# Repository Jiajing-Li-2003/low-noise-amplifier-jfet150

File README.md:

# low-noise-amplifier-jfet150
Open source low-noise amplifier project using JFET150

# 🔊 Low-Noise Amplifier (LNA) Project – JFET150 + OPA211 + Differential Stage

This project documents the design and testing of a **low-noise amplifier (LNA)**, based on a JFET input stage followed by a precision op-amp (OPA211), and a second-stage differential amplifier.

Everything is **open source** and shared for learning, experimentation, and collaboration.

---

## 📌 Table of Contents

- [Overview](#overview)
- [Features](#features)
- [Circuit Design](#circuit-design)
- [Measurements](#measurements)
- [Bill of Materials](#bill-of-materials)
- [Schematic and PCB](#schematic-and-pcb)
- [Usage](#usage)
- [License](#license)
- [Author](#author)

---

## 🔍 Overview

This two-stage amplifier is designed for applications requiring ultra-low noise and high gain:

1. **Low-noise preamp** based on a JFET transistor (JFET150) + OPA211 with ~40 dB gain
2. **Differential amplifier** that adds another 20 dB gain and rejects common-mode noise

---

## ⚙️ Features

| Parameter              | Value                  |
|------------------------|------------------------|
| Total Gain             | ~60 dB (×1000)         |
| Input Noise            | [2 nV/√Hz, @1kHz]      |
| Bandwidth              | [10 Hz – 100 kHz]      |
| Supply Voltage         | 0V-5V                  |
| Input Impedance        | >? MΩ                  |
| Output Impedance       | ~??? Ω                 |

---

## 🔧 Circuit Design

### 🔹 Stage 1 – Low-Noise Preamp

- JFET input (JFET150)
- Precision Op-Amp (OPA211)
- Gain: ~40 dB
- Focus: low noise, high input impedance

### 🔸 Stage 2 – Differential Amplifier

- Differential op-amp topology
- Gain: ~20 dB
- Focus: common-mode noise rejection

---

## 📊 Measurements

The transfer function measurements were performed using two 20 dB attenuators, resulting in a total attenuation of 33 dB applied to the gain:

This is the transfer function of the first stage (blue curve):

This is the transfer function of the second stage:

And there we have the input noise of the amplifier

---

## 🖨️ Schematic and PCB

Browse PCB and schematics online [here](https://kicanvas.org/?github=https%3A%2F%2Fgithub.com%2FJiajing-Li-2003%2Flow-noise-amplifier-jfet150%2Fblob%2Fmain%2Fhardware%2Fampli%2520jfe150%2520searchcoil.kicad_pro).

Files are in the `hardware/` directory.

---

## 🔌 Usage

1. **Power Supply**: +5 V regulated
2. **Input**: Search Coil (a magnetometer)
3. **Output**: Connect to oscilloscope or ADC

> ⚠️ Make sure to use a proper power supply with current limiting

---

## 🪪 License

This project is licensed under the **MIT License** – see the [LICENSE](./LICENSE) file for details.

---

## 🙋 Contributions

Feel free to fork, open issues, or submit pull requests if you want to improve or adapt this project.

---

## 👨‍🔬 Author

Designed by Li Jiajing, This project was carried out during an assistant engineer internship under the supervision of Alexis Jeandet at the Plasma Physics Laboratory (LPP).

---

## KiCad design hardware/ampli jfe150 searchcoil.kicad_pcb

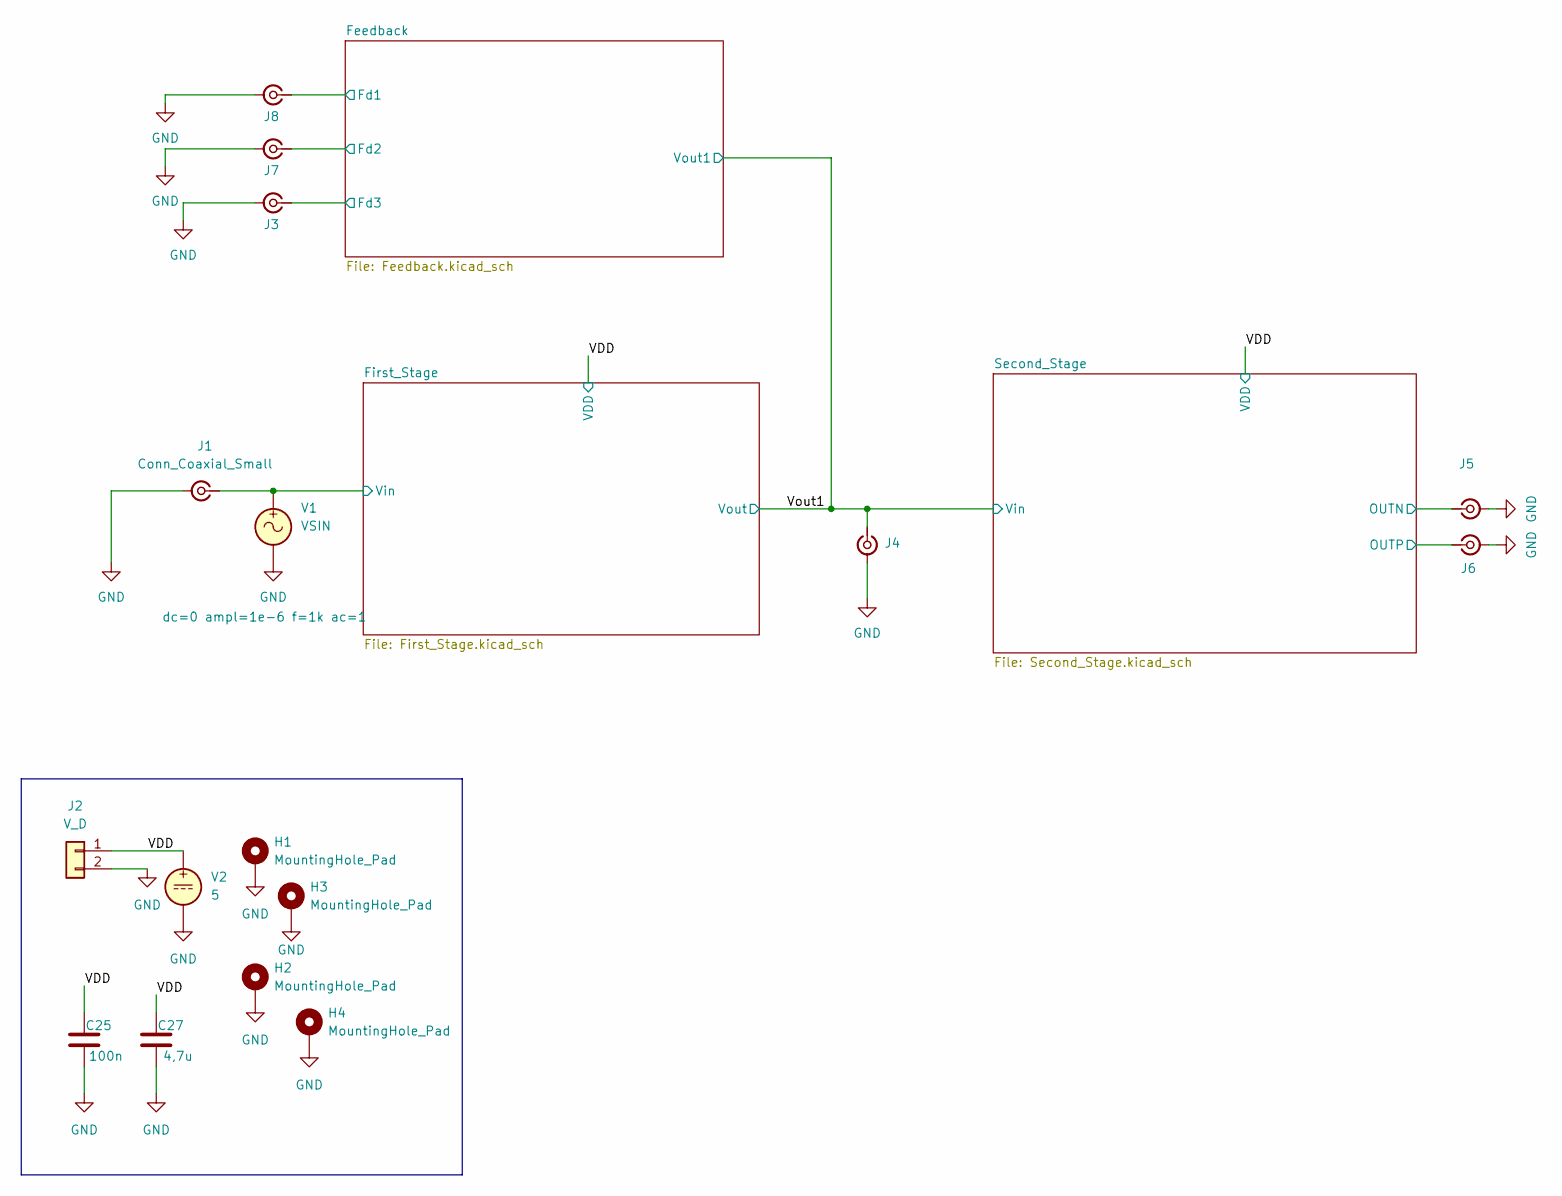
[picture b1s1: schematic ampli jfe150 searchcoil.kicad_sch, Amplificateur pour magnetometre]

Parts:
C25: 100n; C_0603_1608Metric_Pad1.08x0.95mm_HandSolder
C27: 4,7u; C_1206_3216Metric_Pad1.33x1.80mm_HandSolder
H1, H2, H3, H4: MountingHole_Pad; MountingHole_2.2mm_M2_DIN965_Pad
J1, J3, J4, J5, J6, J7, J8: Conn_Coaxial_Small; SMB_Jack_Vertical
J2: V_D; PinHeader_1x02_P2.54mm_Vertical
V1: VSIN
V2: 5

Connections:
/Feedback/Fd1: J8.1 (In); also elsewhere on the board
/Feedback/Fd2: J7.1 (In); also elsewhere on the board
/Feedback/Fd3: J3.1 (In); also elsewhere on the board
/First_Stage/Vin: J1.1 (In), V1.1; also elsewhere on the board
/Second_Stage/OUTN: J5.1 (In); also elsewhere on the board
/Second_Stage/OUTP: J6.1 (In); also elsewhere on the board
/VDD: C25.1, C27.1, J2.1, V2.1; also elsewhere on the board
/Vout1: J4.1 (In); also elsewhere on the board
GND: C25.2, C27.2, H1.1, H2.1, H3.1, H4.1, J1.2 (Ext), J2.2, J3.2 (Ext), J4.2 (Ext), J5.2 (Ext), J6.2 (Ext), J7.2 (Ext), J8.2 (Ext), V1.2, V2.2; also elsewhere on the board

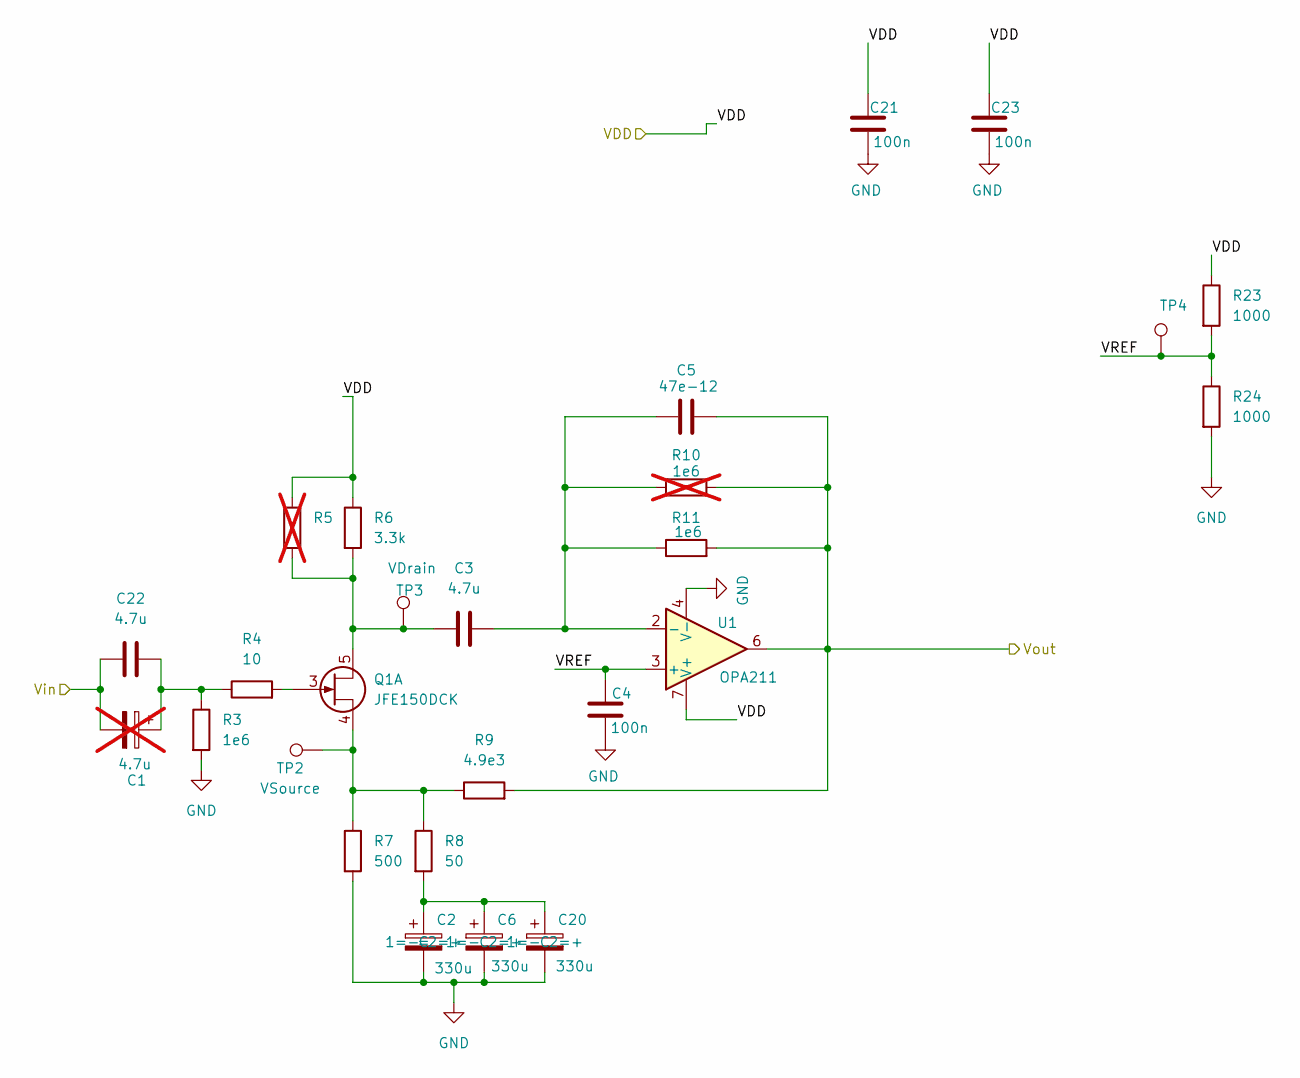
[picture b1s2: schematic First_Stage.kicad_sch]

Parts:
C1: 4.7u; CP_EIA-3528-21_Kemet-B_HandSolder; not fitted
C2, C6, C20: 330u; CP_EIA-6032-28_Kemet-C_HandSolder
C3, C22: 4.7u; C_1206_3216Metric_Pad1.33x1.80mm_HandSolder
C4, C21, C23: 100n; C_0603_1608Metric_Pad1.08x0.95mm_HandSolder
C5: 47e-12; C_0603_1608Metric_Pad1.08x0.95mm_HandSolder
Q1: JFE150DCK; SOT-353_SC-70-5
R3, R11: 1e6; R_0603_1608Metric_Pad0.98x0.95mm_HandSolder
R4: 10; R_0603_1608Metric_Pad0.98x0.95mm_HandSolder
R5: 10e3; R_0603_1608Metric_Pad0.98x0.95mm_HandSolder; not fitted
R6: 3.3k; R_0603_1608Metric_Pad0.98x0.95mm_HandSolder
R7: 500; R_0603_1608Metric_Pad0.98x0.95mm_HandSolder
R8: 50; R_0603_1608Metric_Pad0.98x0.95mm_HandSolder
R9: 4.9e3; R_0603_1608Metric_Pad0.98x0.95mm_HandSolder
R10: 1e6; R_0603_1608Metric_Pad0.98x0.95mm_HandSolder; not fitted
R23, R24: 1000; R_0603_1608Metric_Pad0.98x0.95mm_HandSolder
TP2: VSource; TestPoint_Loop_D1.80mm_Drill1.0mm_Beaded
TP3: VDrain; TestPoint_Loop_D1.80mm_Drill1.0mm_Beaded
TP4: 6V; TestPoint_Loop_D1.80mm_Drill1.0mm_Beaded
U1: OPA211; SOIC-8_3.9x4.9mm_P1.27mm

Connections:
/First_Stage/VREF: C4.1, R23.2, R24.1, TP4.1, U1.3 (+)
/First_Stage/Vin: C1.2, C22.1; also elsewhere on the board
/VDD: C21.1, C23.1, R5.1, R6.1, R23.1, U1.7 (V+); also elsewhere on the board
/Vout1: C5.2, R9.2, R10.2, R11.2, U1.6; also elsewhere on the board
GND: C2.2, C4.2, C6.2, C20.2, C21.2, C23.2, R3.2, R7.2, R24.2, U1.4 (V-); also elsewhere on the board
unnamed: C1.1, C22.2, R3.1, R4.1
unnamed: C2.1, C6.1, C20.1, R8.2
unnamed: C3.1, Q1.5, R5.2, R6.2, TP3.1
unnamed: Q1.3, R4.2
unnamed: Q1.4, R7.1, R8.1, R9.1, TP2.1
unnamed: C3.2, C5.1, R10.1, R11.1, U1.2 (-)

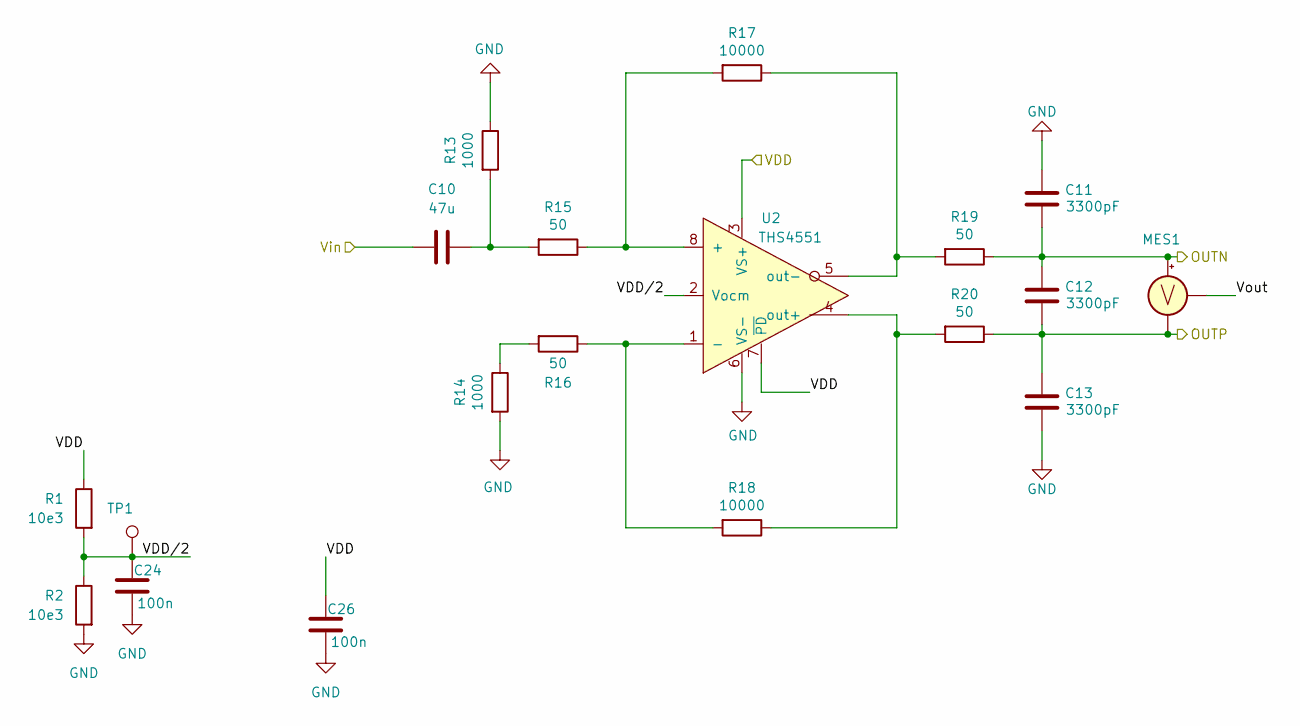
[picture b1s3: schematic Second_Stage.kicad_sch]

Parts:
C10: 47u; C_1206_3216Metric_Pad1.33x1.80mm_HandSolder
C11, C12, C13: 3300pF; C_0603_1608Metric_Pad1.08x0.95mm_HandSolder
C24, C26: 100n; C_0603_1608Metric_Pad1.08x0.95mm_HandSolder
MES1: VOLTMETER_DIFF
R1, R2: 10e3; R_0603_1608Metric_Pad0.98x0.95mm_HandSolder
R13, R14: 1000; R_0603_1608Metric_Pad0.98x0.95mm_HandSolder
R15, R16, R19, R20: 50; R_0603_1608Metric_Pad0.98x0.95mm_HandSolder
R17, R18: 10000; R_0603_1608Metric_Pad0.98x0.95mm_HandSolder
TP1: 6V; TestPoint_Loop_D1.80mm_Drill1.0mm_Beaded
U2: THS4551; VSSOP-8_3x3mm_P0.65mm

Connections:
/Second_Stage/OUTN: C11.2, C12.1, MES1.1 (+), R19.1; also elsewhere on the board
/Second_Stage/OUTP: C12.2, C13.1, MES1.2 (-), R20.1; also elsewhere on the board
/Second_Stage/VDD/2: C24.1, R1.2, R2.1, TP1.1, U2.2 (Vocm)
/VDD: C26.1, R1.1, U2.3 (VS+), U2.7 (~PD); also elsewhere on the board
/Vout1: C10.1; also elsewhere on the board
GND: C11.1, C13.2, C24.2, C26.2, R2.2, R13.1, R14.2, U2.6 (VS-); also elsewhere on the board
unnamed: C10.2, R13.2, R15.2
unnamed: R14.1, R16.2
unnamed: R15.1, R17.2, U2.8 (+)
unnamed: R16.1, R18.2, U2.1 (-)
unnamed: R18.1, R20.2, U2.4 (out+)
unnamed: R17.1, R19.2, U2.5 (out-)

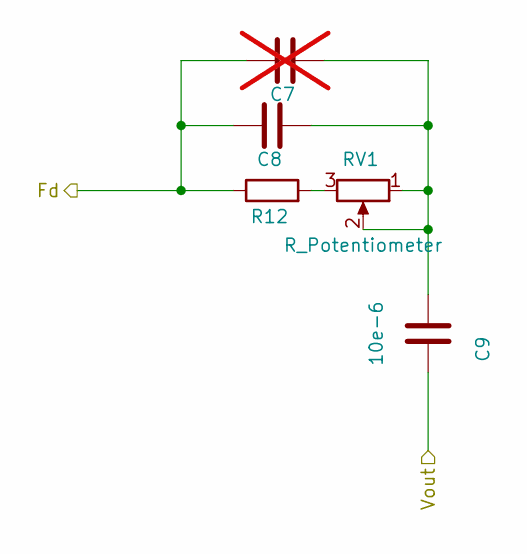
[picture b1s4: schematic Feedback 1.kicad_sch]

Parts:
C7: 10e-12; C_0603_1608Metric_Pad1.08x0.95mm_HandSolder; not fitted
C8: 10e-12; C_0603_1608Metric_Pad1.08x0.95mm_HandSolder
C9: 10e-6; C_1206_3216Metric_Pad1.33x1.80mm_HandSolder
R12: 10e3; R_0603_1608Metric_Pad0.98x0.95mm_HandSolder
RV1: R_Potentiometer; Potentiometer_Bourns_3296W_Vertical

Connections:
/Feedback/Fd1: C7.1, C8.1, R12.1; also elsewhere on the board
/Vout1: C9.1; also elsewhere on the board
unnamed: C7.2, C8.2, C9.2, RV1.1, RV1.2
unnamed: R12.2, RV1.3

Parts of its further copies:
C14, C17: 10e-12; C_0603_1608Metric_Pad1.08x0.95mm_HandSolder
C15, C18: 10e-12; C_0603_1608Metric_Pad1.08x0.95mm_HandSolder; not fitted
C16, C19: 10e-6; C_1206_3216Metric_Pad1.33x1.80mm_HandSolder
R21, R22: 10e3; R_0603_1608Metric_Pad0.98x0.95mm_HandSolder
RV2, RV3: R_Potentiometer; Potentiometer_Bourns_3296W_Vertical

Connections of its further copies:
/Feedback/Fd2: C14.1, C15.1, R21.1; also elsewhere on the board
/Feedback/Fd3: C17.1, C18.1, R22.1; also elsewhere on the board
/Vout1: C16.1, C19.1; also elsewhere on the board
unnamed: C14.2, C15.2, C16.2, RV2.1, RV2.2
unnamed: C17.2, C18.2, C19.2, RV3.1, RV3.2
unnamed: R21.2, RV2.3
unnamed: R22.2, RV3.3

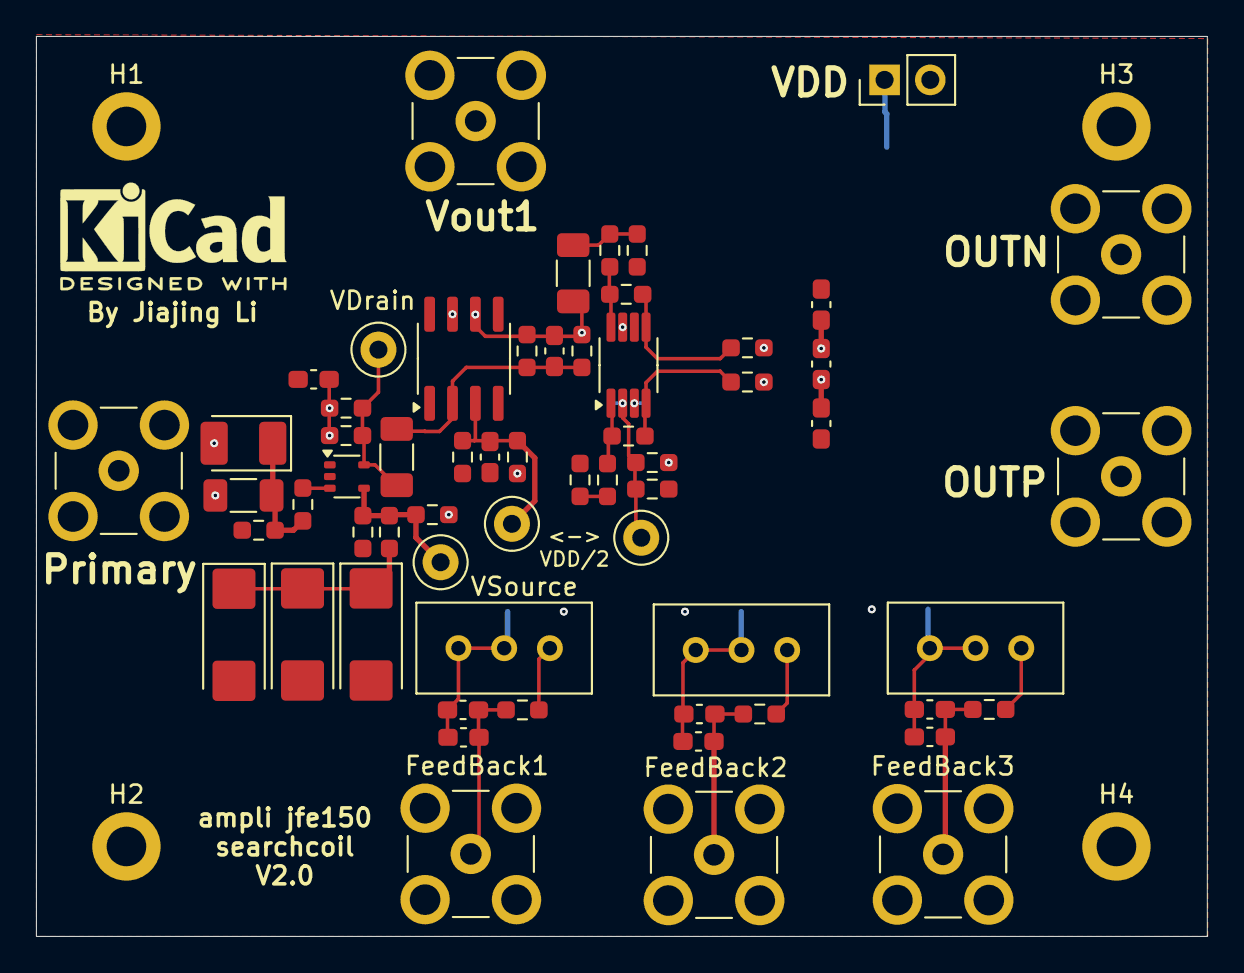
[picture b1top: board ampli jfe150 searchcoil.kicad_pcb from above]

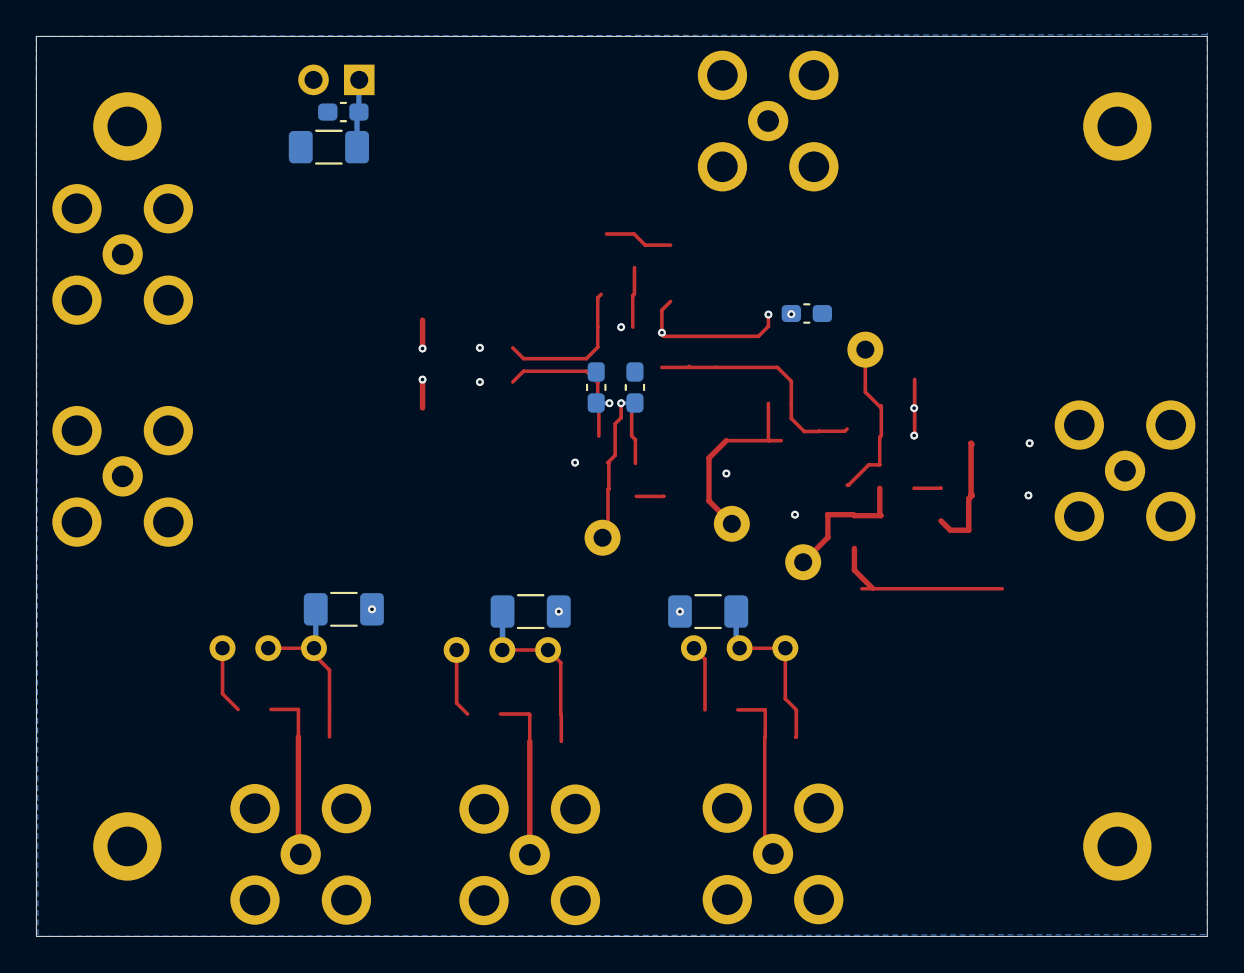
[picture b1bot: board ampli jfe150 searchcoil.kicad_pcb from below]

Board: 4 copper layers, 65.1 x 50.0 mm, 73 parts (8 on the bottom side), 29 nets.

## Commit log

2025-07-21 Create measurement folder
2025-07-21 Update and rename README.md to gain
2025-08-08 Update gain
2025-08-08 Update schematics with latest values
2025-08-08 Add transfer function measurement
2025-08-08 Add transfer function 1 measurement
2025-08-08 Readme modified
2025-08-08 modification
